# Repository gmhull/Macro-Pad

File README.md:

# Macro-Pad
This project was inspired by the ocreeb-12 project <a href='https://github.com/sb-ocr/ocreeb-12'>here</a>.  A big part of this project for me was ordering my first custom PCB.  All my other projects so far have been soldered breadboards.  It took some time to learn, but this process makes the final circuit so much easier to work with.

PCB files were created using EagleCad.  I used Solidworks to create the STL models for printing.  

BOM for the project:
<ul>
  <li>KB2040 board - 1
  <li>1N4148W Diode - 12
  <li>Cherry MX Mechanical Keys - 12
  <li>MX Key Caps - 12
  <li>Neopixel 5050 LEDs - 4
  <li>Custom PCB - 1
  <li>Encoder - 2
  <li>Rubber Feet - 4
  <li>10 kOhm Resistor - 1
  <li>0.1 uF capacitor - 4
</ul>

STL files can be found on my printables page, <a href=''>here</a>.

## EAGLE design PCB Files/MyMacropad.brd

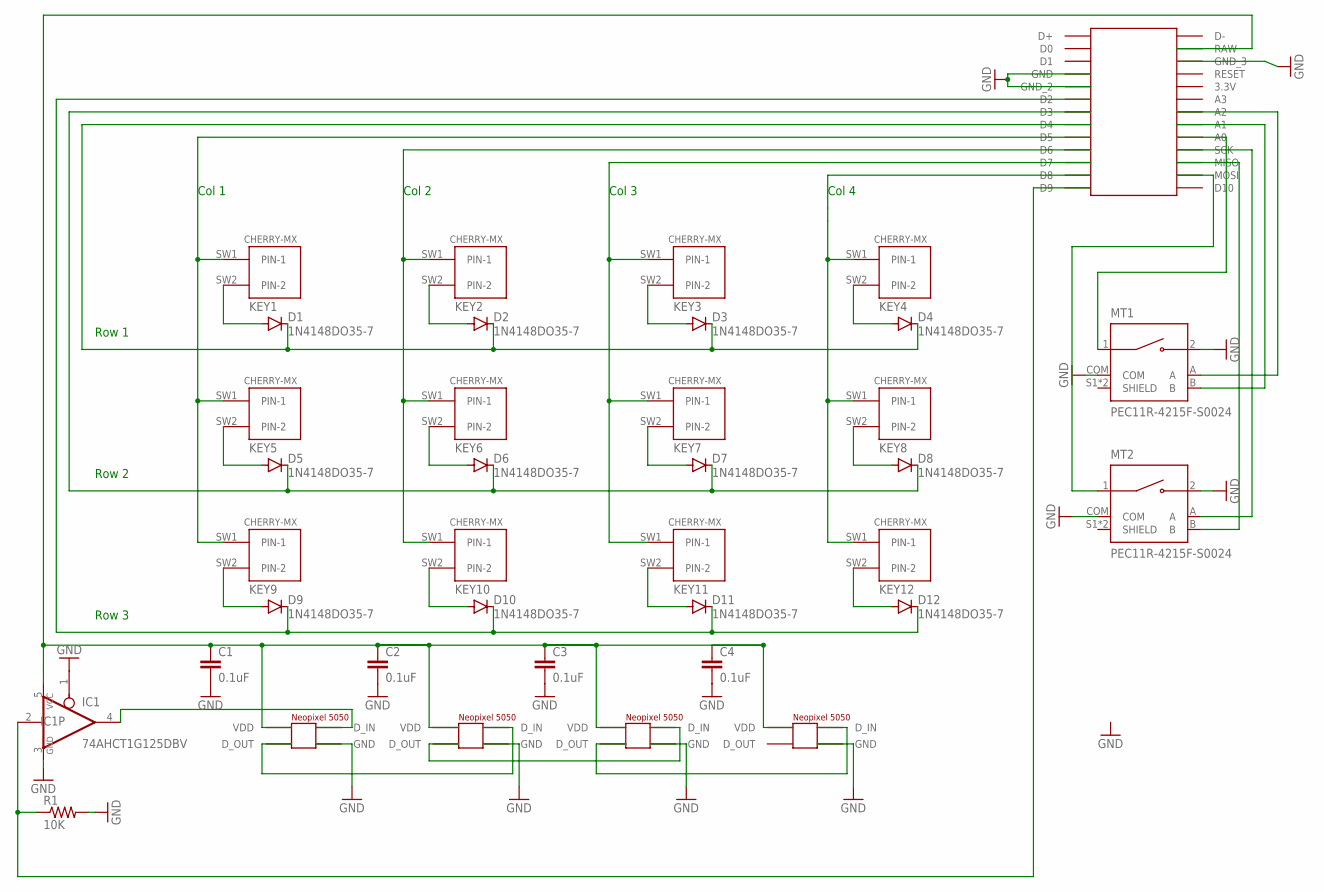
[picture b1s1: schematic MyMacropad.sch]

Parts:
C1, C2, C3, C4: 0.1uF; CAP-PTH-SMALL-KIT
D1, D2, D3, D4, D5, D6, D7, D8, D9, D10, D11, D12: 1N4148DO35-7; DO35-7
IC1: 74AHCT1G125DBV; SOT23-5
KEY1, KEY2, KEY3, KEY4, KEY5, KEY6, KEY7, KEY8, KEY9, KEY10, KEY11, KEY12: CHERRY-MX
MT1, MT2: PEC11R-4215F-S0024; XDCR_PEC11R-4215F-S0024
NEOPIXEL_1, NEOPIXEL_2, NEOPIXEL_3, NEOPIXEL_4: NEOPIXEL_5050
R1: 10K; V234/12
U$5: KB2040

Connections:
GND: C1.2, C2.2, C3.2, C4.2, IC1.1 (OE), IC1.3 (GND), MT1.2, MT1.COM, MT2.2, MT2.COM, NEOPIXEL_1.GND, NEOPIXEL_2.GND, NEOPIXEL_3.GND, NEOPIXEL_4.GND, R1.2, U$5.GND, U$5.GND_2, U$5.GND_3
unnamed: KEY1.SW1 (PIN-1), KEY5.SW1 (PIN-1), KEY9.SW1 (PIN-1), U$5.D5
unnamed: KEY2.SW1 (PIN-1), KEY6.SW1 (PIN-1), KEY10.SW1 (PIN-1), U$5.D6
unnamed: KEY3.SW1 (PIN-1), KEY7.SW1 (PIN-1), KEY11.SW1 (PIN-1), U$5.D7
unnamed: D1.A, KEY1.SW2 (PIN-2)
unnamed: KEY4.SW1 (PIN-1), KEY8.SW1 (PIN-1), KEY12.SW1 (PIN-1), U$5.D8
unnamed: D2.A, KEY2.SW2 (PIN-2)
unnamed: D6.A, KEY6.SW2 (PIN-2)
unnamed: D10.A, KEY10.SW2 (PIN-2)
unnamed: D9.A, KEY9.SW2 (PIN-2)
unnamed: D7.A, KEY7.SW2 (PIN-2)
unnamed: D11.A, KEY11.SW2 (PIN-2)
unnamed: D3.A, KEY3.SW2 (PIN-2)
unnamed: D4.A, KEY4.SW2 (PIN-2)
unnamed: D8.A, KEY8.SW2 (PIN-2)
unnamed: D12.A, KEY12.SW2 (PIN-2)
unnamed: D1.C, D2.C, D3.C, D4.C, U$5.D4
unnamed: IC1.4 (O), NEOPIXEL_1.D_IN
unnamed: NEOPIXEL_3.D_OUT, NEOPIXEL_4.D_IN
unnamed: D5.A, KEY5.SW2 (PIN-2)
unnamed: NEOPIXEL_1.D_OUT, NEOPIXEL_2.D_IN
unnamed: D5.C, D6.C, D7.C, D8.C, U$5.D3
unnamed: D9.C, D10.C, D11.C, D12.C, U$5.D2
unnamed: NEOPIXEL_2.D_OUT, NEOPIXEL_3.D_IN
unnamed: IC1.2 (I), R1.1, U$5.D9
unnamed: C1.1, C2.1, C3.1, C4.1, IC1.5 (VCC), NEOPIXEL_1.VDD, NEOPIXEL_2.VDD, NEOPIXEL_3.VDD, NEOPIXEL_4.VDD, U$5.RAW
unnamed: MT1.A, U$5.A2
unnamed: MT1.B, U$5.A1
unnamed: MT1.1, U$5.A0
unnamed: MT2.1, U$5.MOSI
unnamed: MT2.A, U$5.SCK
unnamed: MT2.B, U$5.MISO

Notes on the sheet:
Col 1
Col 2
Col 3
Col 4
Row 1
Row 2
Row 3

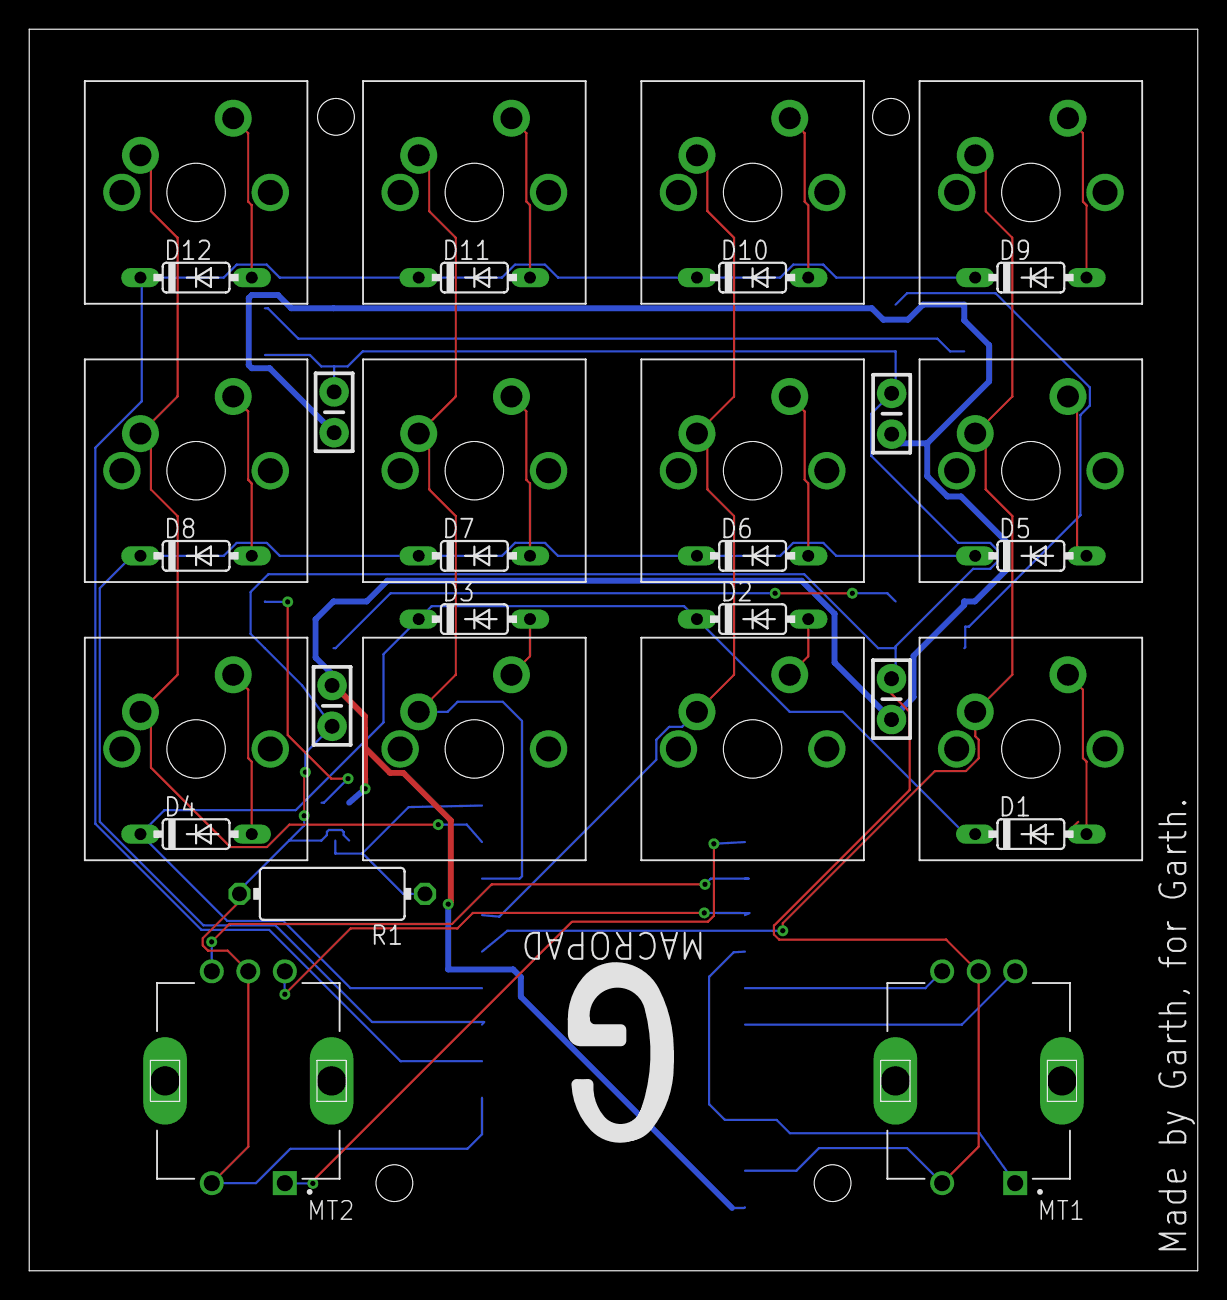
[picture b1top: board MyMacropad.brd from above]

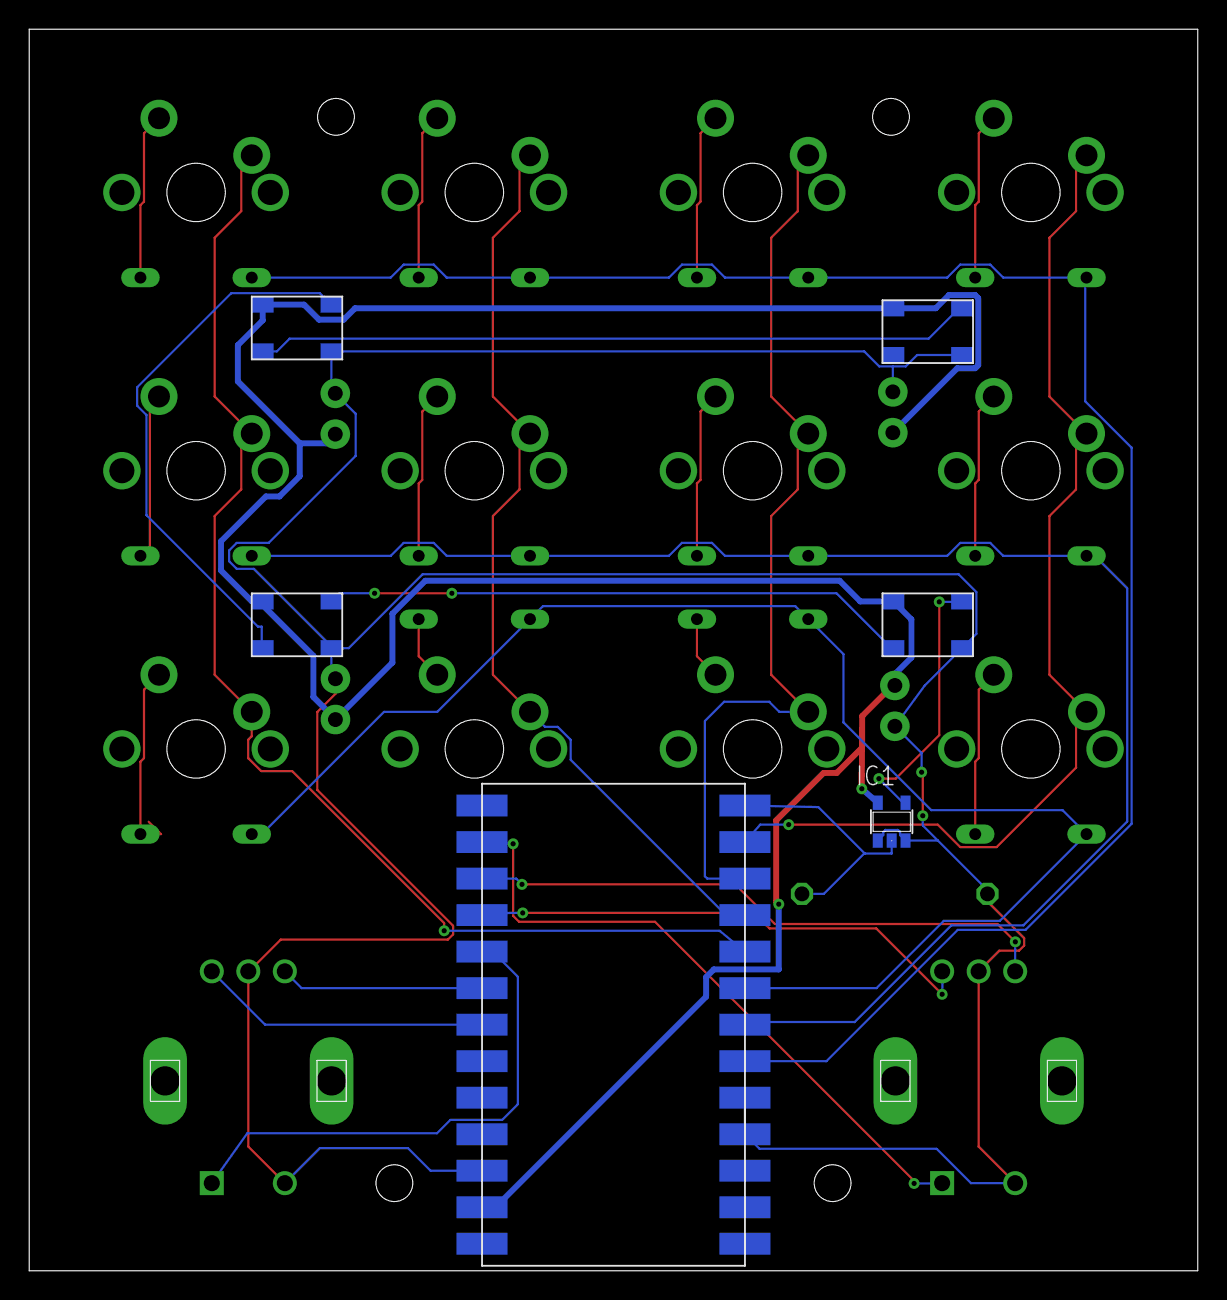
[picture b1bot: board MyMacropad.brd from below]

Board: 2 copper layers, 80.0 x 85.0 mm, 37 parts (6 on the bottom side), 32 nets.

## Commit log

2023-06-25 Added PCD Files
2023-06-25 Added STL Files
2023-06-25 update gitignore

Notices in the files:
parts and their libraries:
SparkFun-Capacitors: Licensing: Creative Commons ShareAlike 4.0 International - https://creativecommons.org/licenses/by-sa/4.0
